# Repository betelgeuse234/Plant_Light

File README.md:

# Plant_Light
Indoor plant light controlled via an AtMega328P
This has evolved and had documents or multiple different designs in it. I need to updeate this description and reorganize to make it clear what designs are what.

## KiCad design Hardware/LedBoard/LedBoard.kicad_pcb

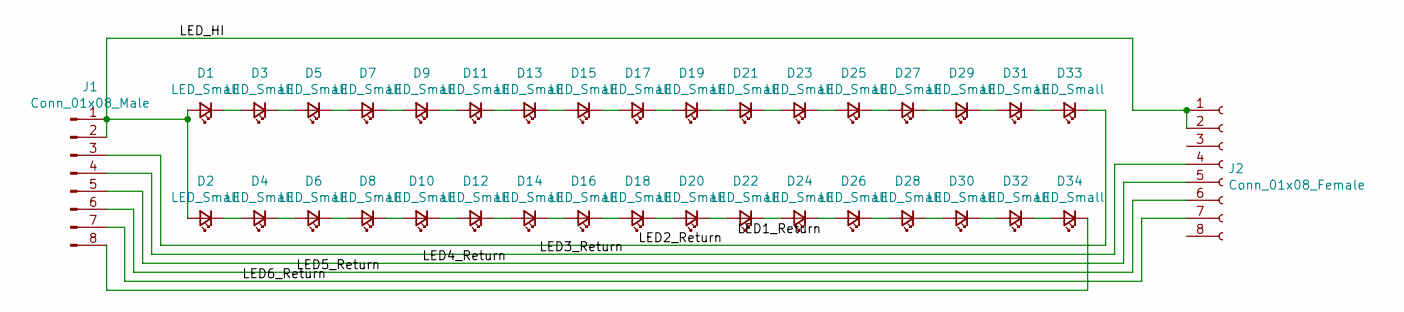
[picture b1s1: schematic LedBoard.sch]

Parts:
D1, D2, D3, D4, D5, D6, D7, D8, D9, D10, D11, D12, D13, D14, D15, D16, D17, D18, D19, D20, D21, D22, D23, D24, D25, D26, D27, D28, D29, D30, D31, D32, D33, D34: LED_Small; Cree_J_Series_3030
J1: Conn_01x08_Male; PinHeader_1x08_P2.54mm_Horizontal
J2: Conn_01x08_Female; PinHeader_1x08_P2.54mm_Horizontal

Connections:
/LED2_Return: D33.1 (K), J1.3
/LED3_Return: J1.4, J2.4
/LED4_Return: J1.5, J2.5
/LED5_Return: J1.6, J2.6
/LED6_Return: J1.7, J2.7
/LED_HI: D1.2 (A), D2.2 (A), J1.1, J1.2, J2.1, J2.2
unnamed: D1.1 (K), D3.2 (A)
unnamed: D2.1 (K), D4.2 (A)
unnamed: D3.1 (K), D5.2 (A)
unnamed: D4.1 (K), D6.2 (A)
unnamed: D5.1 (K), D7.2 (A)
unnamed: D6.1 (K), D8.2 (A)
unnamed: D7.1 (K), D9.2 (A)
unnamed: D10.1 (K), D12.2 (A)
unnamed: D8.1 (K), D10.2 (A)
unnamed: D11.1 (K), D13.2 (A)
unnamed: D9.1 (K), D11.2 (A)
unnamed: D12.1 (K), D14.2 (A)
unnamed: D13.1 (K), D15.2 (A)
unnamed: D14.1 (K), D16.2 (A)
unnamed: D15.1 (K), D17.2 (A)
unnamed: D16.1 (K), D18.2 (A)
unnamed: D17.1 (K), D19.2 (A)
unnamed: D18.1 (K), D20.2 (A)
unnamed: D19.1 (K), D21.2 (A)
unnamed: D20.1 (K), D22.2 (A)
unnamed: D21.1 (K), D23.2 (A)
unnamed: D22.1 (K), D24.2 (A)
unnamed: D23.1 (K), D25.2 (A)
unnamed: D24.1 (K), D26.2 (A)
unnamed: D25.1 (K), D27.2 (A)
unnamed: D26.1 (K), D28.2 (A)
unnamed: D27.1 (K), D29.2 (A)
unnamed: D28.1 (K), D30.2 (A)
unnamed: D29.1 (K), D31.2 (A)
unnamed: D30.1 (K), D32.2 (A)
unnamed: D31.1 (K), D33.2 (A)
unnamed: D32.1 (K), D34.2 (A)
unnamed: D34.1 (K), J1.8

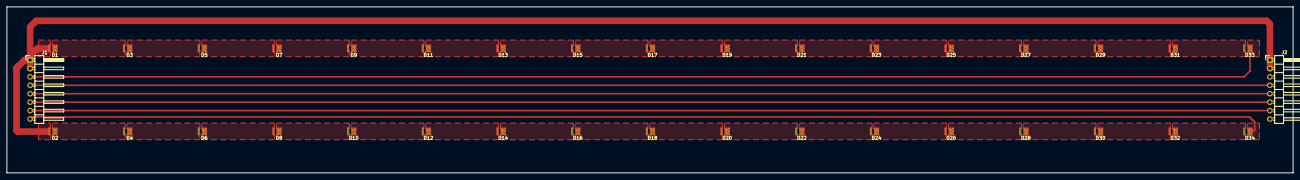
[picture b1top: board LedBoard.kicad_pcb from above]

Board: 2 copper layers, 387.5 x 50.0 mm, 36 parts (0 on the bottom side), 39 nets.

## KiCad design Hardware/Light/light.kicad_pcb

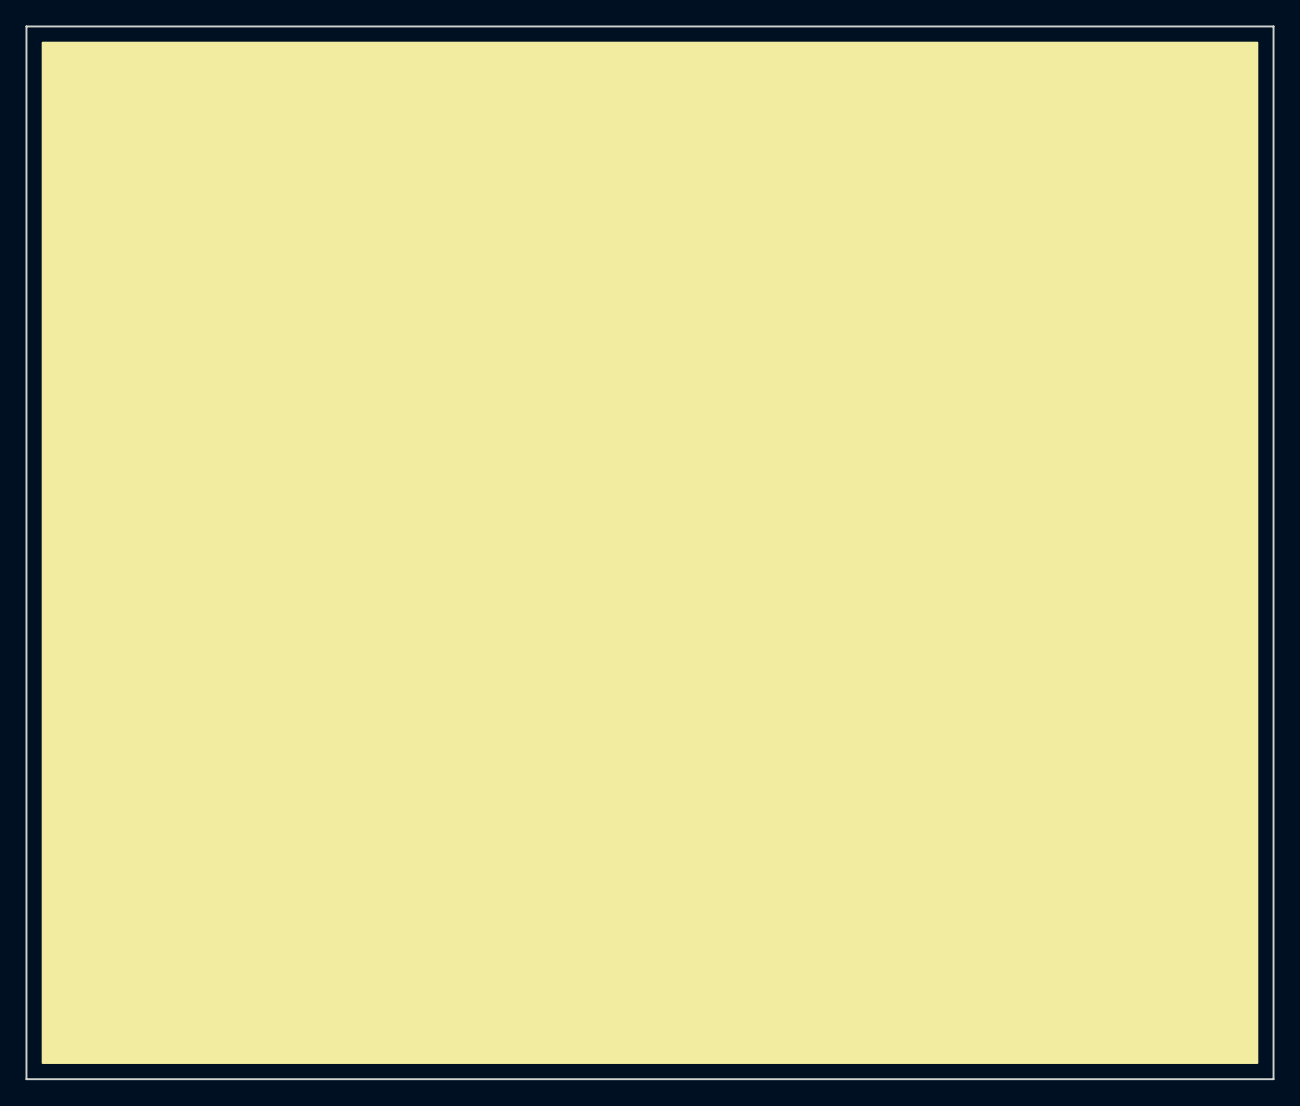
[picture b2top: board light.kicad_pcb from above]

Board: 2 copper layers, 97.8 x 82.6 mm, 28 parts (0 on the bottom side), 21 nets.

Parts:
C1, C2, C3, C4, C5: 100pF; C_0805_HandSoldering
J1: Conn_01x06_Male; JST_VH_S6P-VH_2x6x3.96mm_Horizontal
J2: Conn_01x02_Male; JST_VH_S2P-VH_2x2x3.96mm_Horizontal
J3: Conn_01x05_Male; JST_VH_S5P-VH_2x5x3.96mm_Horizontal
R1: 0.025R; R_2512_HandSoldering
R2, R4, R5, R6, R7, R8, R9, R10, R11, R12: 10k; R_1206_HandSoldering
R3: 1.2k; R_1206_HandSoldering
R13, R14, R15: 0R; R_1206_HandSoldering
U1: AD8211; SOT-23-5_HandSoldering
U2, U3: MCP3021; SOT-23-5_HandSoldering
U4: MCP4541; MSOP-8_3x3mm_Pitch0.65mm
U5: TCA9548APWR; TSSOP-24_4.4x7.8mm_Pitch0.65mm

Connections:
+5V: C1.1, C2.1, C3.1, C4.1, C5.1, J3.1, R4.2, R5.2, R6.2, R7.2, R8.2, R9.2, R10.2, R11.2, R12.2, U1.5, U2.1, U3.1, U4.8, U5.24
/Ain2: U1.1, U2.3
/Ain3: R2.1, R3.2, U3.3
/RESET: J3.3, R12.1, U5.3
/SCL: J3.5, R10.1, U5.22
/SCL0: R4.1, U4.2, U5.5
/SCL1: R6.1, U2.5, U5.7
/SCL2: R8.1, U3.5, U5.9
/SDA: J3.4, R11.1, U5.23
/SDA0: R5.1, U4.3, U5.4
/SDA1: R7.1, U2.4, U5.6
/SDA2: R9.1, U3.4, U5.8
GND: C1.2, C2.2, C3.2, C4.2, C5.2, J3.2, R13.1, R14.1, R15.1, U1.2, U2.2, U3.2, U4.1, U4.4, U4.7, U5.10, U5.11, U5.12, U5.13, U5.14, U5.15, U5.16, U5.17, U5.18, U5.19, U5.20
LED+: J2.2, R1.1, R2.2, U1.4
unnamed: R13.2, U5.21
unnamed: R14.2, U5.2
unnamed: R15.2, U5.1
PSU+: J1.3, J1.4, R1.2, U1.3
PSU-: J1.5, J1.6, J2.1, R3.1
VR1: J1.1, U4.6
VR2: J1.2, U4.5

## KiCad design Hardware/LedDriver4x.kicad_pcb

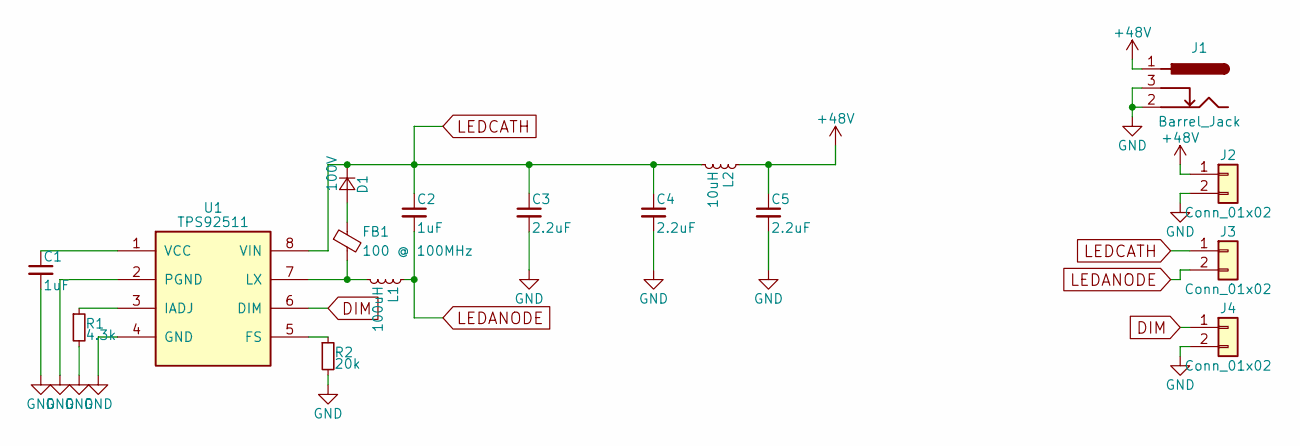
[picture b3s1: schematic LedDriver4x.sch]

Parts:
C1, C2: 1uF; C_0805_HandSoldering
C3, C4, C5: 2.2uF; CP_Radial_D5.0mm_P2.00mm
D1: 100V; D_SMA_Handsoldering
FB1: 100 @ 100MHz; C_0805_HandSoldering
J1: Barrel_Jack; BARREL_JACK
J2, J3, J4: Conn_01x02; Pin_Header_Angled_1x02_Pitch2.54mm
L1: 100uH; L_Radial_D8.7mm_P5.00mm_Fastron_07HCP
L2: 10uH; L_0805_HandSoldering
R1: 4.3k; R_0603_HandSoldering
R2: 20k; R_0603_HandSoldering
U1: TPS92511; SOIC-8_3.9x4.9mm_Pitch1.27mm

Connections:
+48V: C5.1, J1.1, J2.1, L2.1
DIM: J4.1, U1.6 (DIM)
GND: C1.2, C3.2, C4.2, C5.2, J1.2, J1.3, J2.2, J4.2, R1.2, R2.2, U1.2 (PGND), U1.4 (GND)
LEDANODE: C2.2, J3.2, L1.1
LEDCATH: C2.1, C3.1, C4.1, D1.1 (K), J3.1, L2.2, U1.8 (VIN)
unnamed: C1.1, U1.1 (VCC)
unnamed: D1.2 (A), FB1.1
unnamed: FB1.2, L1.2, U1.7 (LX)
unnamed: R1.1, U1.3 (IADJ)
unnamed: R2.1, U1.5 (FS)

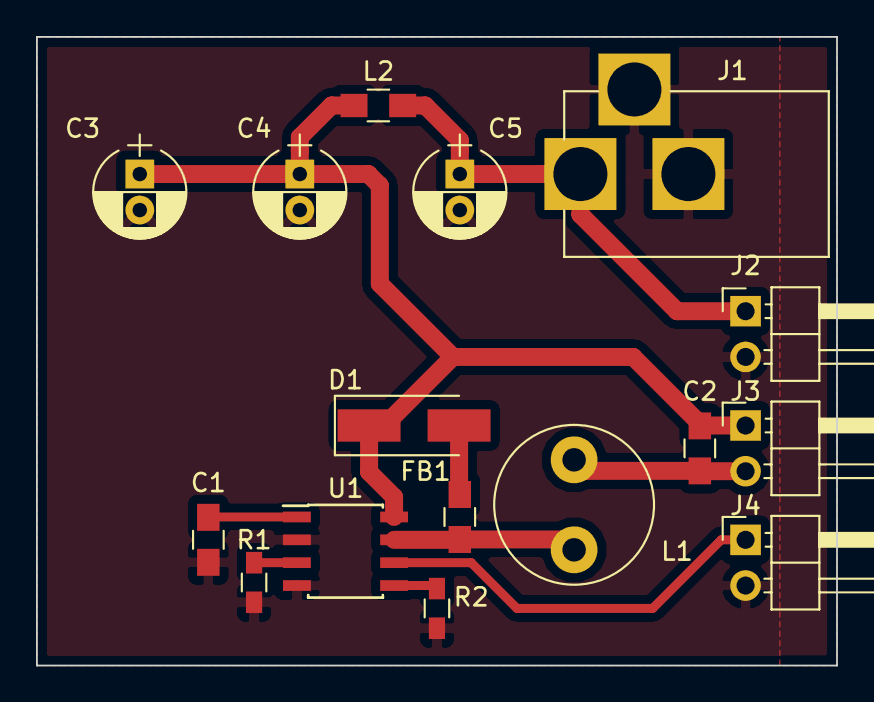
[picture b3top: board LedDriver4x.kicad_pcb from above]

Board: 2 copper layers, 44.4 x 34.9 mm, 16 parts (0 on the bottom side), 10 nets.

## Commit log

2017-02-25 Added atmel autosave files to gitignore
2017-02-25 Added File Format Along with useful files from Laser Cutter Project
2017-03-01 Data Sheet for Mico and COB Leds
2017-11-30 Yes
    Idk what happened
2017-11-30 Data Sheet
    Data sheet
2017-12-05 Post Review Changes
    Changes per request of John Fritz
2017-12-05 Stuff
    things
2019-10-05 Changes bro
    Changes bro
2020-05-16 Put together schematic for SMPS
2020-05-25 Removed .bak. Refined schematic.
2020-11-30 -Added board for 48 inch light bars. -They utilize 3 shorter PCBs roughly 48/3 in length -Currently I just manually run wires to correct the pathes between the boards
